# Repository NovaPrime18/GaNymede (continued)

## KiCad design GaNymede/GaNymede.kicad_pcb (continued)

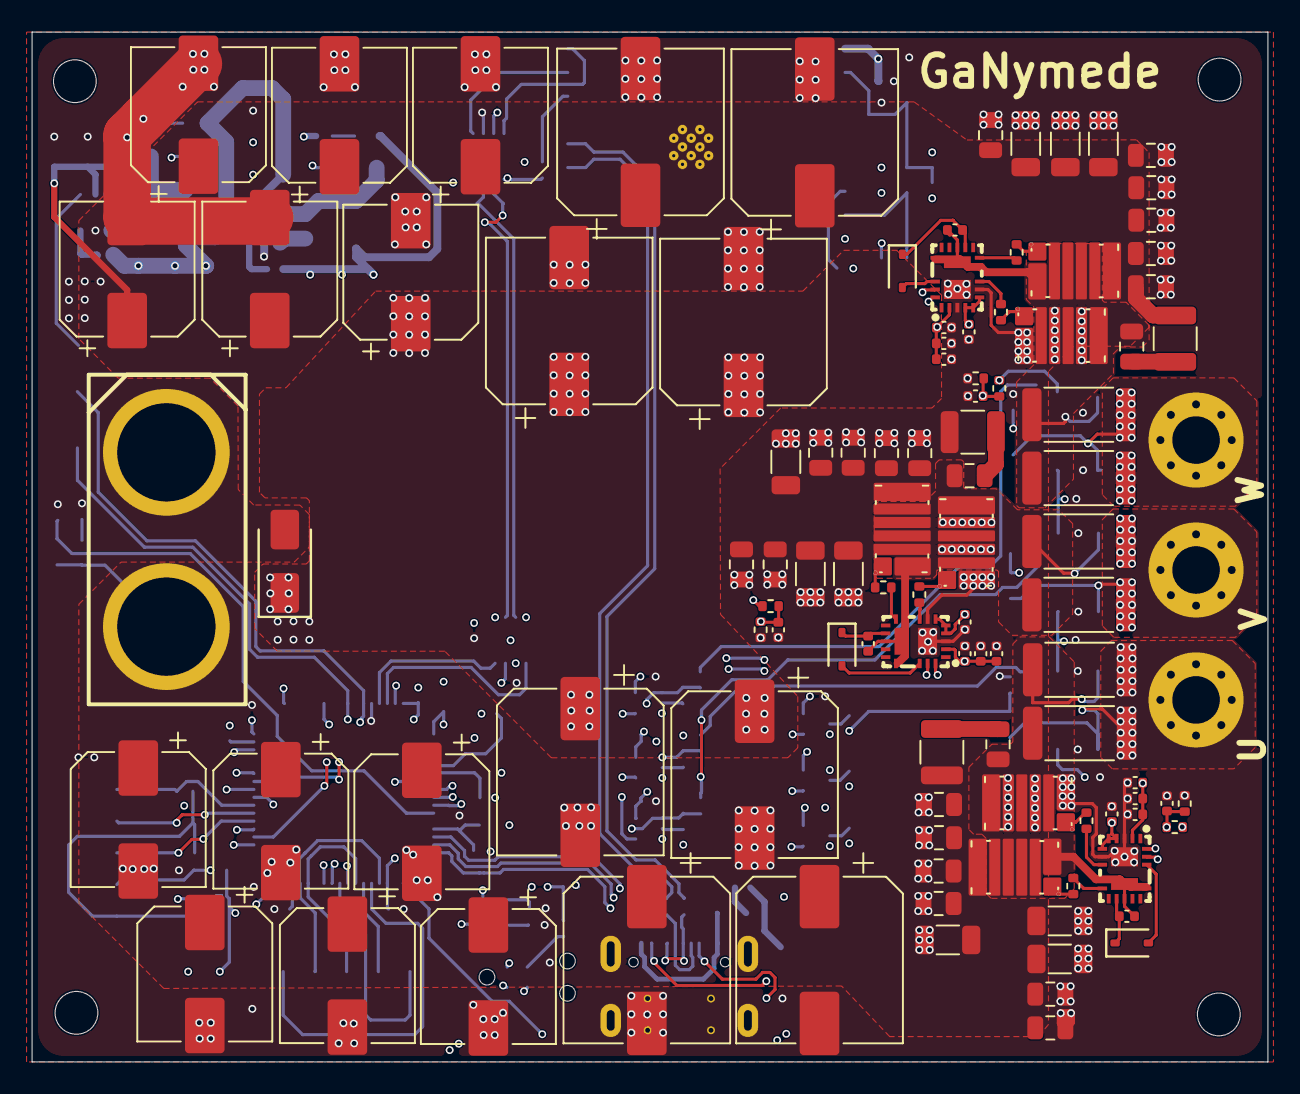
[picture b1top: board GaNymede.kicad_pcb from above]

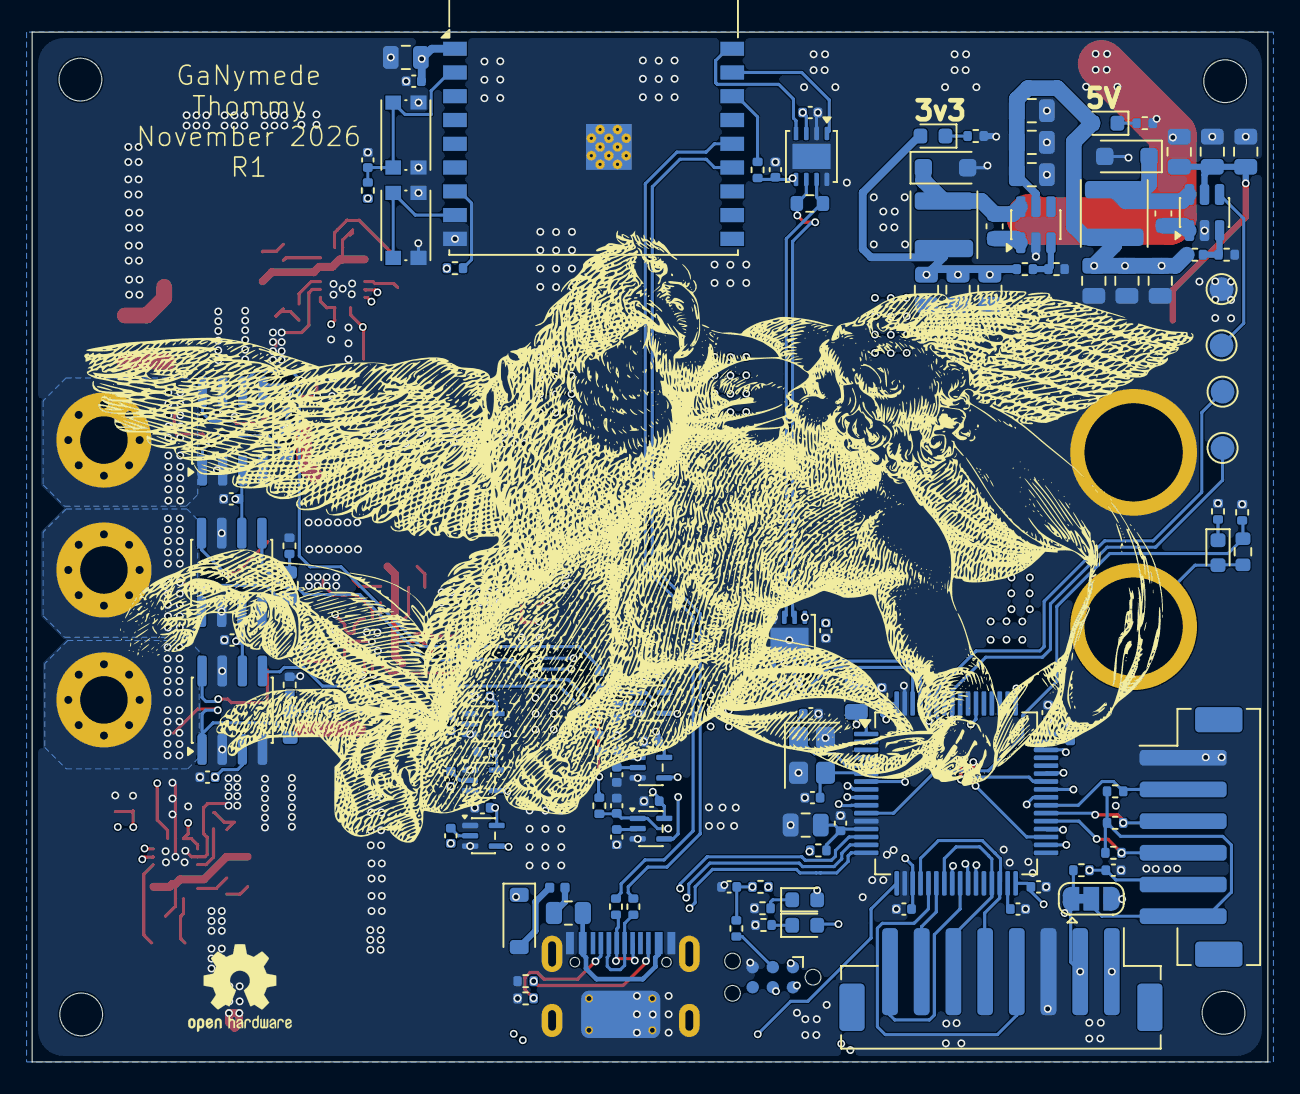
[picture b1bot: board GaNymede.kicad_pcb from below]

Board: 6 copper layers, 78.0 x 65.0 mm, 236 parts (126 on the bottom side), 110 nets.

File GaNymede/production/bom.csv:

Designator,Footprint,Quantity,Value,LCSC Part #
"C1, C15, C16, C18, C19, C20, C21, C29, C3, C30, C32, C36, C37, C4, C47, C5, C50, C52, C53, C58, C6, C60, C63, C7, C71, C77",0402,26,100nF,C307331
"C10, C13, C14, C17, C27, C28, C39, C9",0402,8,2.2uF,C20539421
"C11, C12",0402,2,15pF,C1548
"C110, C111, C112, C113, C115, C116, C117, C118",CP_Elec_10x10,8,100uF 80V,C487410
C119,0402,1,100n,
"C122, C123, C124, C125, C126, C127, C128, C129, C130, C136, C137, C138, C139, C147, C148, C33, C35, C38",0805,18,1uF 100V,C5370002
"C134, C135, C140, C141, C142, C143, C144, C145, C146",1206,9,4.7uF 100V,C22367839
"C150, C151, C152, C153, C154, C155, C156, C157, C158, C159, C160, C161",CP_Elec_8x10,12,47uF 100V,C48935391
"C2, C34, C8",0805,3,10uF,C440198
"C201, C202, C203",0805,3,2.2nF 100V,C107136
C31,0402,1,1uF,C52923
"C48, C57, C66",0402,3,15nF,C114405
"C49, C59, C68",0402,3,1nF,C1523
"C51, C64, C70, C74, C75, C76",0402,6,1uF,
"C54, C67, C73",0402,3,100nF,
"C55, C90",0603,2,100n X7R 100V,C15725
"C56, C61, C62, C86, C87, C88",0805,6,1u X7R 100V,C5370002
"C65, C69, C72, C91, C92, C93",0805,6,10u X7R 25V,C3039694
D1,0603,1,Red,C2286
"D14, D23",D_SOD-123F,2,MBR1H100SFT3G,C235757
D2,0603,1,Green,C84267
"D22, D24, D25",0603,3,LED,C2286
D27,D_SMA,1,SMAJ60A,C42394398
D4,D_SOD-123,1,BAV16W,C459527
"D6, D7, D8",D_SOD-323,3,BAT46WS,C7502692
F2,0805,1,0.5A,C2833485
FB2,0402,1,600R@100MHz,C76884
J1,TH_XT90PB-M,1,XT90,C3040688
J4,JST_PH_B6B-PH-SM4-TB_1x06-1MP_P2.00mm_Vertical,1,Hall,C471518
J5,JST_PH_B8B-PH-SM4-TB_1x08-1MP_P2.00mm_Vertical,1,COMM,C495548
J7,TYPE-C-SMD_HX-TYPE-C-16PIN,1,"Connector, USB-TYPE-C-16P",C2927039
"L2, L3",L_Sunlord_SWPA4030S,2,22uH 1A 0.29Ohm,C167883
"Q1, Q2, Q3, Q4, Q5, Q6",D0606F_100V,6,EPC2361,
"R1, R42, R43",0402,3,22,C25092
R10,0402,1,4.7,C25121
"R100, R101, R102, R97, R98, R99",2512,6,0.5mR,
"R105, R106",0402,2,5.1k,C25905
"R11, R12, R14, R18, R48, R49, R50",0402,7,10k,C25744
"R13, R15, R16, R17, R19, R20",0402,6,2.2,
"R2, R3, R67, R72, R78",0402,5,1k,C11702
"R201, R202, R203",1210,3,1,C2974068
"R39, R46, R51, R58",0603,4,56k,C23206
"R4, R5, R6",0402,3,2k2,
"R40, R47, R52, R59",0402,4,2k2,C25879
R41,0603,1,220,C22962
R7,0402,1,10k,
"R74, R75, R76",0402,3,10k @25°C,C77131
"R77, R95",0402,2,1k,C106235
R79,0402,1,50k,C25897
R86,0402,1,33k 1%,C138003
R92,0402,1,10k 0.1%,C190095
R93,0402,1,57.6k 0.1%,C852849
R94,0402,1,10k,C2906861
"SW1, SW2",SW_Push_1P1T_NO_CK_KMR2,2,KMR211NGLFS,C221676
TP1,TestPoint_Pad_D1.5mm,1,Enable,
TP2,TestPoint_Pad_D1.5mm,1,TestPoint,
TP3,TestPoint_Pad_D1.5mm,1,Red,
TP4,TestPoint_Pad_D1.5mm,1,Green,
U1,LQFP-64_10x10mm_P0.5mm,1,STM32F405RGTx,C15742
"U10, U11, U12, U13, U14, U17",SOT-353_SC-70-5,6,74LVC1G66,C97489
"U15, U16",SOT-23-6,2,LMR16006XDDCR,C87080
"U18, U7",HVSON-8-1EP_3x3mm_P0.65mm_EP1.6x2.4mm,2,TJA1051TK-3,C2875699
"U19, U20, U21",WQFN-19_L4.0-W3.0-P0.50-BL-EP_LMG1210RVRR,3,LMG1210,C2677136
"U3, U4, U5",SOIC-8_3.9x4.9mm_P1.27mm,3,INA240A1D,C1346458
U8,ESP32-C3-WROOM-02,1,ESP32-C3-WROOM-02,C2934560
Y1,Crystal_SMD_3225-4Pin_3.2x2.5mm,1,8M,C2682775
